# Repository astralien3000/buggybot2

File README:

This is the repository of buggybot 2, a four-legged robot which will take part to the robotic contest Eurobot.

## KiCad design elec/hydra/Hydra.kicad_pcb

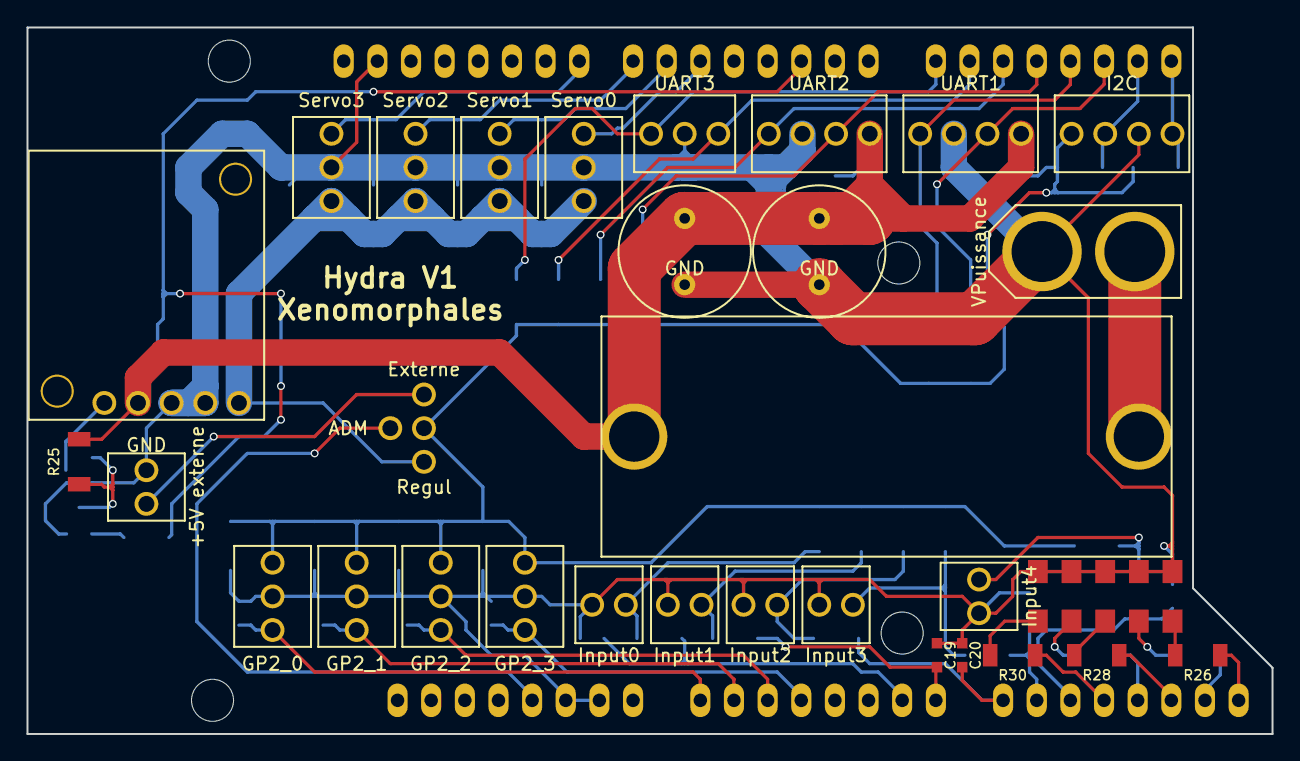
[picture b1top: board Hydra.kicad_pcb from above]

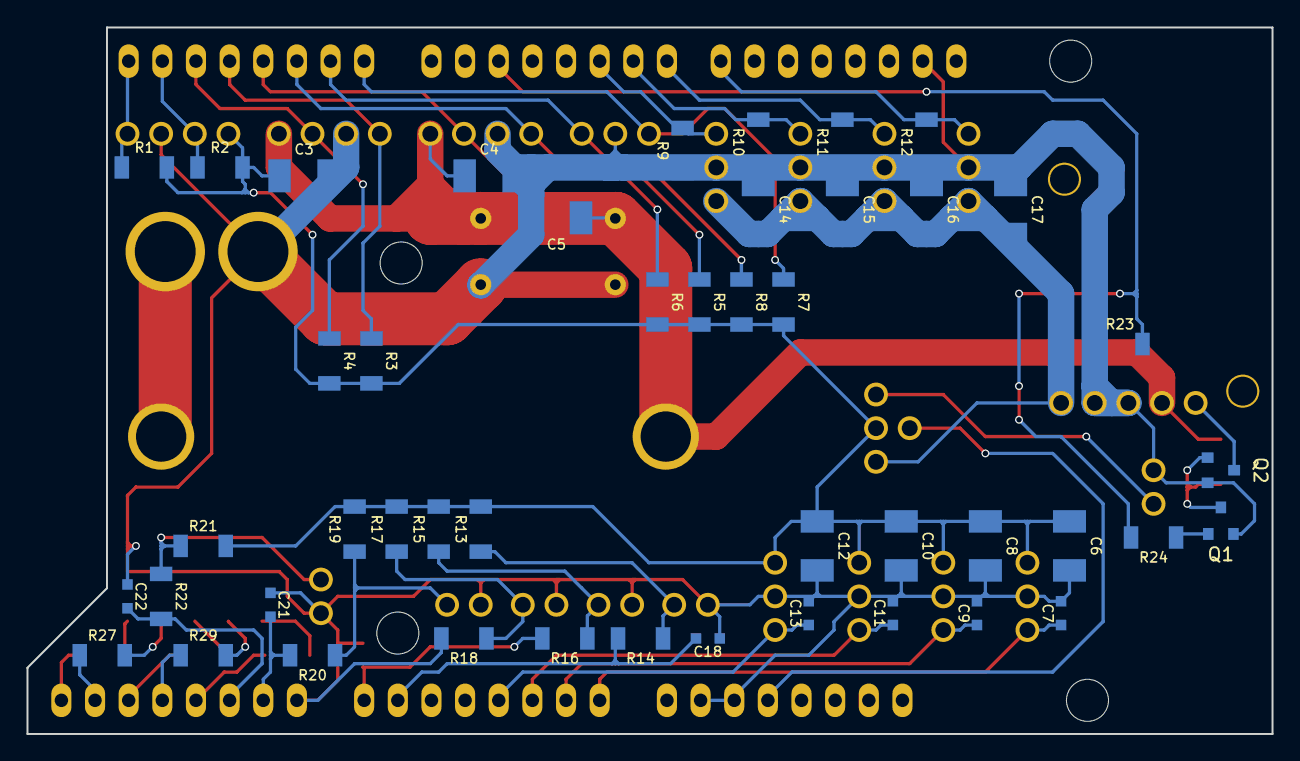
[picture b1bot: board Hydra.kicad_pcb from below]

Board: 2 copper layers, 94.0 x 53.3 mm, 82 parts (46 on the bottom side), 47 nets.

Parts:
+5V externe: Bat5V; Conn_01x02
C1, C2: 330µF; C_Radial
C3, C4, C5, C6, C8, C10, C12, C14, C15, C16, C17: 10µF; C_CMS1210
C7, C9, C11, C13: 100nF; C_CMS0603
C18, C19, C20, C21, C22: 1µF; C_CMS0603
D1, D2, D3, D4, D5: LED; LED_Green_CMS
F1: FUSE 20A; Fuse
GP2_0, GP2_1, GP2_2, GP2_3: GP2; Conn_01x03
I2C: I2C_1; Conn_01x04
Input0, Input1, Input2, Input3, Input4: Switch; Conn_01x02
P20: Jumper5V; 3-state_jumper
Q1, Q2: Q_NPN_BEC; SOT-23-3-bipolar-transistor
R1, R2, R3, R4, R5, R6, R7, R8, R9, R10, R11, R12, R23: 10kΩ; R_CMS1206
R13, R15, R17, R19, R21: 100kΩ; R_CMS1206
R14, R16, R18, R20, R22: 18kΩ; R_CMS1206
R24, R25: 1kΩ; R_CMS1206
R26, R27, R28, R29, R30: 200Ω; R_CMS1206
Regul1: Regul; Pololu_D24V50F5
SHIELD1: ARDUINO_MEGA_SHIELD
Servo0, Servo1, Servo2, Servo3: Servo; Conn_01x03
UART1: UART_1; Conn_01x04
UART2: UART_2; Conn_01x04
UART3: UART_3; Conn_01x03
VPuissance: Bat7.5V; Power_Conn_01x02

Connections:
/Arduino/+5VADM: P20.2, SHIELD1.5V
/Arduino/GND: +5V externe.1, C1.2, C2.2, C3.1, C4.1, C5.1, C6.1, C7.1, C8.1, C9.1, C10.1, C11.1, C12.1, C13.1, C14.2, C15.2, C16.2, C17.2, C18.2, C19.2, C20.2, C21.2, C22.2, D1.1, D2.1, D3.1, D4.1, D5.1, GP2_0.2, GP2_1.2, GP2_2.2, GP2_3.2, I2C.2, Input0.1, Input1.1, Input2.1, Input3.1, Input4.1, Q1.2, Q2.2, R9.2, R10.2, R11.2, R12.2, R23.2, Regul1.3, Regul1.4, SHIELD1.GND1, SHIELD1.GND2, SHIELD1.GND3, Servo0.2, Servo1.2, Servo2.2, Servo3.2, UART1.2, UART2.2, UART3.2, VPuissance.1
/Arduino/GP2_0: C7.2, GP2_0.1, SHIELD1.AD0
/Arduino/GP2_1: C9.2, GP2_1.1, SHIELD1.AD1
/Arduino/GP2_2: C11.2, GP2_2.1, SHIELD1.AD2
/Arduino/GP2_3: C13.2, GP2_3.1, SHIELD1.AD3
/Arduino/Input0: C18.1, R14.1, SHIELD1.AD6
/Arduino/Input1: C19.1, R16.1, SHIELD1.AD7
/Arduino/Input2: C20.1, R18.1, SHIELD1.AD8
/Arduino/Input3: C21.1, R20.1, SHIELD1.AD9
/Arduino/Input4: C22.1, R22.1, SHIELD1.AD10
/Arduino/RX1: R4.2, SHIELD1.19, UART1.3
/Arduino/RX2: R6.2, SHIELD1.17, UART2.3
/Arduino/RX3: R8.2, SHIELD1.15, UART3.3
/Arduino/RegulEnable: R23.1, R24.1, SHIELD1.2
/Arduino/SCL: I2C.1, R1.2, SHIELD1.21
/Arduino/SDA: I2C.3, R2.2, SHIELD1.20
/Arduino/TX1: R3.2, SHIELD1.18, UART1.1
/Arduino/TX2: R5.2, SHIELD1.16, UART2.1
/Arduino/TX3: R7.2, SHIELD1.14, UART3.1
/Com/+5V: C3.2, C6.2, C8.2, C10.2, C12.2, GP2_0.3, GP2_1.3, GP2_2.3, GP2_3.3, I2C.4, P20.4, R1.1, R2.1, R3.1, R4.1, R5.1, R6.1, R7.1, R8.1, R13.1, R15.1, R17.1, R19.1, R21.1
/Com/+7.5V: C1.1, C2.1, C4.2, C5.2, F1.1, R25.2, Regul1.2, UART1.4, UART2.4
/Servo1/+5V: C14.1, C15.1, C16.1, C17.1, P20.1, Regul1.5, Servo0.1, Servo1.1, Servo2.1, Servo3.1
/Servo1/PWM: R9.1, SHIELD1.5, Servo0.3
/Servo2/PWM: R10.1, SHIELD1.6, Servo1.3
/Servo3/PWM: R11.1, SHIELD1.7, Servo2.3
/Servo4/PWM: R12.1, SHIELD1.8, Servo3.3
unnamed: D1.2, R26.1
unnamed: D2.2, R27.1
unnamed: D3.2, R28.1
unnamed: D4.2, R29.1
unnamed: D5.2, R30.1
unnamed: F1.2, VPuissance.2
unnamed: Input0.2, R13.2, R14.2
unnamed: Input1.2, R15.2, R16.2
unnamed: Input2.2, R17.2, R18.2
unnamed: Input3.2, R19.2, R20.2
unnamed: Input4.2, R21.2, R22.2
unnamed: +5V externe.2, P20.3
unnamed: Q1.1, R24.2
unnamed: Q1.3, Q2.1, R25.1
unnamed: Q2.3, Regul1.1
unnamed: R26.2, SHIELD1.AD15
unnamed: R27.2, SHIELD1.AD14
unnamed: R28.2, SHIELD1.AD13
unnamed: R29.2, SHIELD1.AD12
unnamed: R30.2, SHIELD1.AD11

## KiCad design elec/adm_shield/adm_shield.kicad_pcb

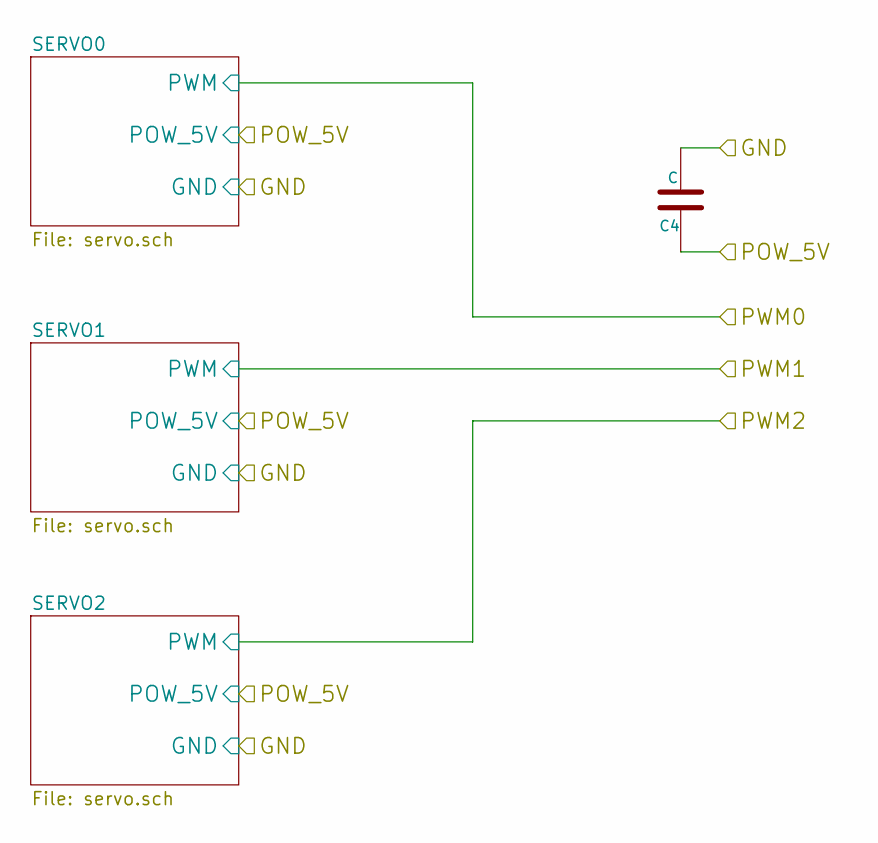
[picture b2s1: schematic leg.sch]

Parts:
C1: C

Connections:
/ALIM/GND: C1.2; also elsewhere on the board
/ALIM/POW_5V: C1.1; also elsewhere on the board

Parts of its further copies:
C2, C3, C4: C

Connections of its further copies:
/ALIM/GND: C2.2, C3.2, C4.2; also elsewhere on the board
/ALIM/POW_5V: C2.1, C3.1, C4.1; also elsewhere on the board

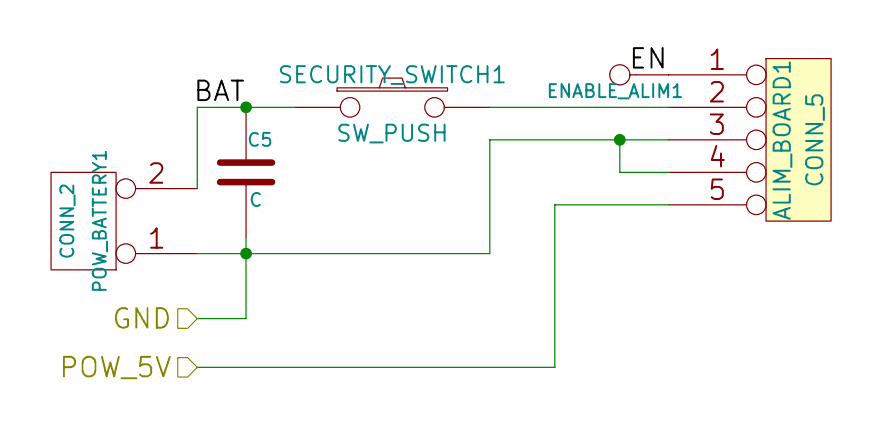
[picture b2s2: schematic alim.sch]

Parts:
ALIM_BOARD1: CONN_5
C5: C
ENABLE_ALIM1: CONN_1
POW_BATTERY1: CONN_2
SECURITY_SWITCH1: SW_PUSH

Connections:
/ALIM/BAT: C5.1, POW_BATTERY1.2 (PM), SECURITY_SWITCH1.1
/ALIM/EN: ALIM_BOARD1.1, ENABLE_ALIM1.1
/ALIM/GND: ALIM_BOARD1.3, ALIM_BOARD1.4, C5.2, POW_BATTERY1.1; also elsewhere on the board
/ALIM/POW_5V: ALIM_BOARD1.5; also elsewhere on the board
unnamed: ALIM_BOARD1.2, SECURITY_SWITCH1.2

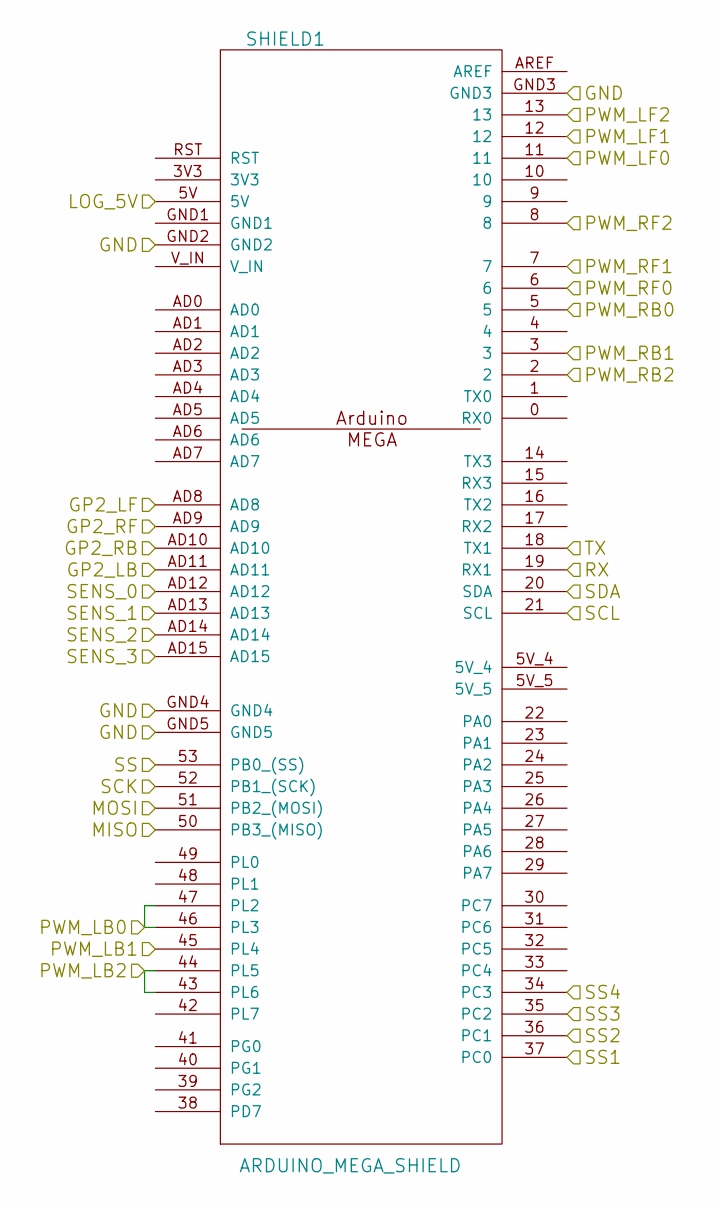
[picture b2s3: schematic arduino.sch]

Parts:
SHIELD1: ARDUINO_MEGA_SHIELD

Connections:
/ALIM/GND: SHIELD1.GND2, SHIELD1.GND3, SHIELD1.GND4, SHIELD1.GND5; also elsewhere on the board
/ARDUINO/GP2_LB: SHIELD1.AD11; also elsewhere on the board
/ARDUINO/GP2_LF: SHIELD1.AD8; also elsewhere on the board
/ARDUINO/GP2_RB: SHIELD1.AD10; also elsewhere on the board
/ARDUINO/GP2_RF: SHIELD1.AD9; also elsewhere on the board
/ARDUINO/LOG_5V: SHIELD1.5V; also elsewhere on the board
/ARDUINO/MISO: SHIELD1.50 (PB3_(MISO)); also elsewhere on the board
/ARDUINO/MOSI: SHIELD1.51 (PB2_(MOSI)); also elsewhere on the board
/ARDUINO/RX: SHIELD1.19 (RX1); also elsewhere on the board
/ARDUINO/SCK: SHIELD1.52 (PB1_(SCK)); also elsewhere on the board
/ARDUINO/SCL: SHIELD1.21 (SCL); also elsewhere on the board
/ARDUINO/SDA: SHIELD1.20 (SDA); also elsewhere on the board
/ARDUINO/SS: SHIELD1.53 (PB0_(SS)); also elsewhere on the board
/ARDUINO/SS1: SHIELD1.37 (PC0); also elsewhere on the board
/ARDUINO/SS2: SHIELD1.36 (PC1); also elsewhere on the board
/ARDUINO/SS3: SHIELD1.35 (PC2); also elsewhere on the board
/ARDUINO/SS4: SHIELD1.34 (PC3); also elsewhere on the board
/ARDUINO/TX: SHIELD1.18 (TX1); also elsewhere on the board
/GPIO/GPIO0: SHIELD1.AD12; also elsewhere on the board
/GPIO/GPIO1: SHIELD1.AD13; also elsewhere on the board
/GPIO/GPIO2: SHIELD1.AD14; also elsewhere on the board
/GPIO/GPIO3: SHIELD1.AD15; also elsewhere on the board
/LEG_LB/PWM0: SHIELD1.46 (PL3), SHIELD1.47 (PL2); also elsewhere on the board
/LEG_LB/PWM1: SHIELD1.45 (PL4); also elsewhere on the board
/LEG_LB/PWM2: SHIELD1.43 (PL6), SHIELD1.44 (PL5); also elsewhere on the board
/LEG_LF/PWM0: SHIELD1.11; also elsewhere on the board
/LEG_LF/PWM1: SHIELD1.12; also elsewhere on the board
/LEG_LF/PWM2: SHIELD1.13; also elsewhere on the board
/LEG_RB/PWM0: SHIELD1.5; also elsewhere on the board
/LEG_RB/PWM1: SHIELD1.3; also elsewhere on the board
/LEG_RB/PWM2: SHIELD1.2; also elsewhere on the board
/LEG_RF/PWM0: SHIELD1.6; also elsewhere on the board
/LEG_RF/PWM1: SHIELD1.7; also elsewhere on the board
/LEG_RF/PWM2: SHIELD1.8; also elsewhere on the board

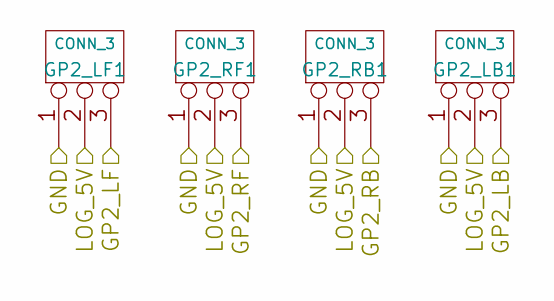
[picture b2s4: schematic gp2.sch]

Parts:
GP2_LB1, GP2_LF1, GP2_RB1, GP2_RF1: CONN_3

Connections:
/ALIM/GND: GP2_LB1.1, GP2_LF1.1, GP2_RB1.1, GP2_RF1.1; also elsewhere on the board
/ARDUINO/GP2_LB: GP2_LB1.3; also elsewhere on the board
/ARDUINO/GP2_LF: GP2_LF1.3; also elsewhere on the board
/ARDUINO/GP2_RB: GP2_RB1.3; also elsewhere on the board
/ARDUINO/GP2_RF: GP2_RF1.3; also elsewhere on the board
/ARDUINO/LOG_5V: GP2_LB1.2 (PM), GP2_LF1.2 (PM), GP2_RB1.2 (PM), GP2_RF1.2 (PM); also elsewhere on the board

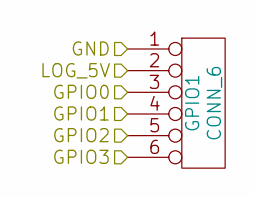
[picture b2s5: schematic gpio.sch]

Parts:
GPIO1: CONN_6

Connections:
/ALIM/GND: GPIO1.1; also elsewhere on the board
/ARDUINO/LOG_5V: GPIO1.2; also elsewhere on the board
/GPIO/GPIO0: GPIO1.3; also elsewhere on the board
/GPIO/GPIO1: GPIO1.4; also elsewhere on the board
/GPIO/GPIO2: GPIO1.5; also elsewhere on the board
/GPIO/GPIO3: GPIO1.6; also elsewhere on the board

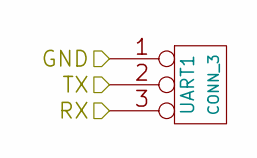
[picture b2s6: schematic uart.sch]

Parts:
UART1: CONN_3

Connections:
/ALIM/GND: UART1.1; also elsewhere on the board
/ARDUINO/RX: UART1.3; also elsewhere on the board
/ARDUINO/TX: UART1.2 (PM); also elsewhere on the board

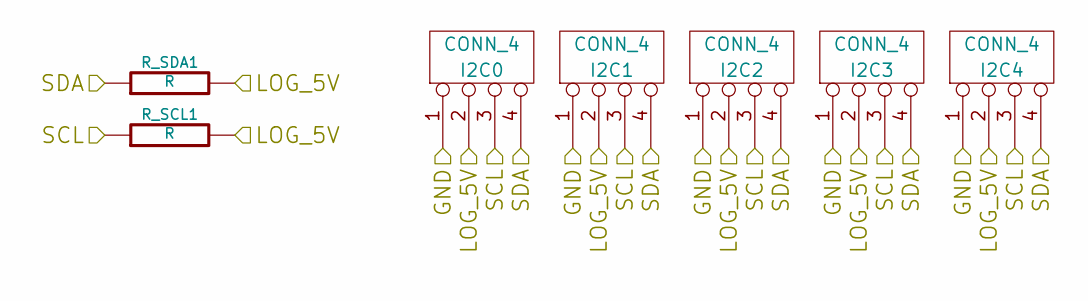
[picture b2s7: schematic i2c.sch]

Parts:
I2C0, I2C1, I2C2, I2C3, I2C4: CONN_4
R_SCL1: R
R_SDA1: R

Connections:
/ALIM/GND: I2C0.1, I2C1.1, I2C2.1, I2C3.1, I2C4.1; also elsewhere on the board
/ARDUINO/LOG_5V: I2C0.2, I2C1.2, I2C2.2, I2C3.2, I2C4.2, R_SCL1.2, R_SDA1.2; also elsewhere on the board
/ARDUINO/SCL: I2C0.3, I2C1.3, I2C2.3, I2C3.3, I2C4.3, R_SCL1.1; also elsewhere on the board
/ARDUINO/SDA: I2C0.4, I2C1.4, I2C2.4, I2C3.4, I2C4.4, R_SDA1.1; also elsewhere on the board

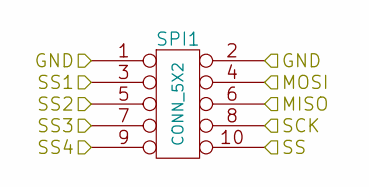
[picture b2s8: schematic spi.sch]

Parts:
SPI1: CONN_5X2

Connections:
/ALIM/GND: SPI1.1, SPI1.2; also elsewhere on the board
/ARDUINO/MISO: SPI1.6; also elsewhere on the board
/ARDUINO/MOSI: SPI1.4; also elsewhere on the board
/ARDUINO/SCK: SPI1.8; also elsewhere on the board
/ARDUINO/SS: SPI1.10; also elsewhere on the board
/ARDUINO/SS1: SPI1.3; also elsewhere on the board
/ARDUINO/SS2: SPI1.5; also elsewhere on the board
/ARDUINO/SS3: SPI1.7; also elsewhere on the board
/ARDUINO/SS4: SPI1.9; also elsewhere on the board

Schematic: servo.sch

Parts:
SERVO_LF1: CONN_3

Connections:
/ALIM/GND: SERVO_LF1.1; also elsewhere on the board
/ALIM/POW_5V: SERVO_LF1.2 (PM); also elsewhere on the board
/LEG_LF/PWM1: SERVO_LF1.3; also elsewhere on the board

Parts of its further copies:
SERVO_LB0, SERVO_LB1, SERVO_LB2: CONN_3
SERVO_LF0, SERVO_LF2: CONN_3
SERVO_RB0, SERVO_RB1, SERVO_RB2: CONN_3
SERVO_RF0, SERVO_RF1, SERVO_RF2: CONN_3

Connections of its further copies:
/ALIM/GND: SERVO_LB0.1, SERVO_LB1.1, SERVO_LB2.1, SERVO_LF0.1, SERVO_LF2.1, SERVO_RB0.1, SERVO_RB1.1, SERVO_RB2.1, SERVO_RF0.1, SERVO_RF1.1, SERVO_RF2.1; also elsewhere on the board
/ALIM/POW_5V: SERVO_LB0.2 (PM), SERVO_LB1.2 (PM), SERVO_LB2.2 (PM), SERVO_LF0.2 (PM), SERVO_LF2.2 (PM), SERVO_RB0.2 (PM), SERVO_RB1.2 (PM), SERVO_RB2.2 (PM), SERVO_RF0.2 (PM), SERVO_RF1.2 (PM), SERVO_RF2.2 (PM); also elsewhere on the board
/LEG_LB/PWM0: SERVO_LB0.3; also elsewhere on the board
/LEG_LB/PWM1: SERVO_LB1.3; also elsewhere on the board
/LEG_LB/PWM2: SERVO_LB2.3; also elsewhere on the board
/LEG_LF/PWM0: SERVO_LF0.3; also elsewhere on the board
/LEG_LF/PWM2: SERVO_LF2.3; also elsewhere on the board
/LEG_RB/PWM0: SERVO_RB0.3; also elsewhere on the board
/LEG_RB/PWM1: SERVO_RB1.3; also elsewhere on the board
/LEG_RB/PWM2: SERVO_RB2.3; also elsewhere on the board
/LEG_RF/PWM0: SERVO_RF0.3; also elsewhere on the board
/LEG_RF/PWM1: SERVO_RF1.3; also elsewhere on the board
/LEG_RF/PWM2: SERVO_RF2.3; also elsewhere on the board

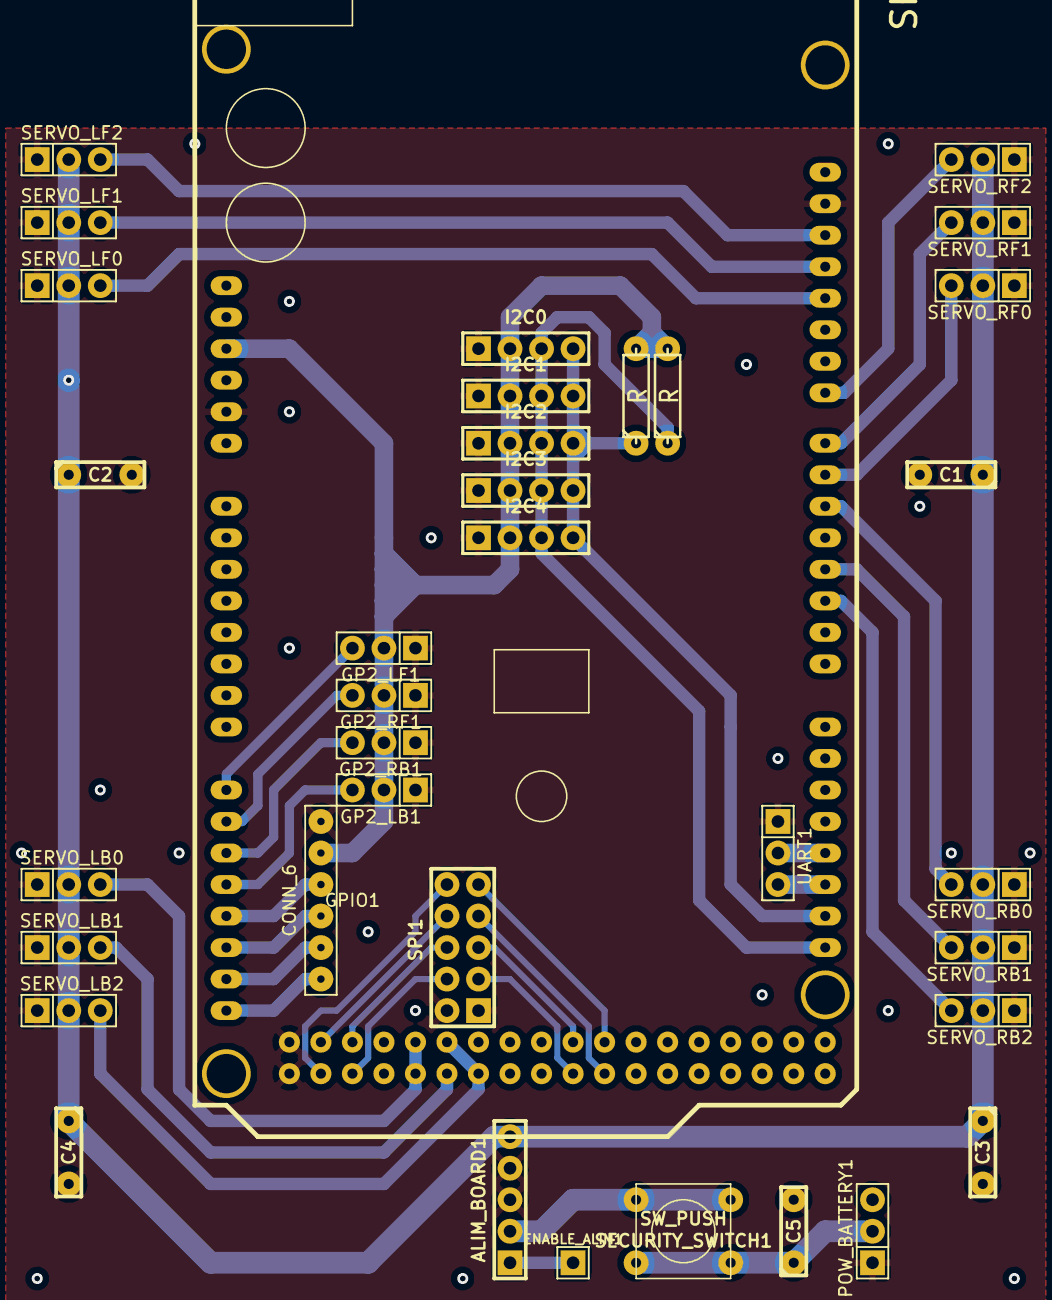
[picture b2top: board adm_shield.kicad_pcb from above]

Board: 2 copper layers, 36 parts (0 on the bottom side), 38 nets.

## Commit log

2014-10-30 Begining
2014-10-30 Added tr_homogene.mac
2014-10-30 MGD, begining
2014-11-01 Added gitignore
2014-11-01 Added old test of multipwm
2014-11-01 Added .hex files to gitignore
2014-11-01 Multipwm example now compiles
2014-11-01 Added servo_config
2014-11-01 Separation of servo_tester
2014-11-02 Created a shell for calibration
2014-11-02 Added QtCreator files
2014-11-02 Added .gitignore to qtcreator dir
2014-11-12 Added MGI
2014-11-12 Renamed some files
2014-11-12 Moved some utils function in a separate file
2014-11-12 added some fake measures
2014-11-12 added cinematic model
2014-11-14 Modified a little MGI and MGD
2014-11-16 Changed compile chain to cmake
2014-11-18 Added .gitignore to build dir in calib
2014-11-18 Added coeff eq paul
2014-11-19 Added paul8 function
2014-11-19 Added .gitignore to meca/solve
2014-11-24 Mesh generation script.
2014-11-25 Added MGI and MGD to blender simulation
2014-11-28 simu MGD and MGI
2014-11-28 Communicaton between robot and computer works ! The robot can "walk". Servo are calibrated
2015-02-27 Begin to designe arduino shield.
2015-02-27 Modified servos (120Hz -> 60Hz)
2015-02-27 Continuation of Kicad schematics.
2015-02-28 Schematics finished ?
2015-02-28 Begining of the PCB.
2015-02-28 PCB almost finished ?
2015-02-28 First version PCB.
2015-03-01 Shield V2 (PCB begining)
2015-03-01 Before routing.
2015-03-01 PCB almost finished !
2015-03-01 PCB FINISHED ! + Correction of schematics.
2015-03-01 Modified ServoTester init. Modified Servos pin mapping. Added a security to SetAngle (0 div).
2015-03-02 PCB v3 !
2015-03-02 V3.1 ?
2015-03-06 New wlaking algo. PCB v4
2015-03-06 PCB v4.1
2015-03-14 Awesome new control program is working !!!
2015-03-15 Better connection management
2015-03-18 Turn and climb animations
2015-04-06 Added accelero test.
2015-04-11 Added astrabot protocol.
2015-04-11 Separated ap parser
2015-04-12 Test comm with arduino
2015-04-22 Added forgotten files. Added bumper management.
2015-04-26 GP2 managed. Added python AP parser.
2015-04-27 Added adc module.
2015-04-27 Added files to .gitignore
2015-04-27 Moved soft directories
2015-04-27 Moved files in soft/embed (WARNING -> doesn't compile)
2015-04-27 Protocol test now compiles !
2015-04-27 ADC test compiles !
2015-04-27 Added cleaning script to embed
2015-04-27 ap_server now compiles !
2015-04-29 Updated MGD model. MGI have to be changed, but gives values near from Blender's ones.
2015-04-29 Updated MGI to new meca
2015-04-29 New MGI implemented in python !!!
2015-05-01 NEW CALIB (WEB) APPLICATION
2015-05-01 Added run.sh script
2015-05-01 Debug MGI !
2015-05-02 Cleaned MGD code
2015-05-02 Cleaned blend file
2015-05-02 Improved animation
2015-05-02 Comm blender - robot works !
2015-05-03 Animation PASSMURAILLE
2015-05-03 Blender-independent code
2015-05-03 Exported crawl anim
2015-05-03 Debug save.py
2015-05-03 debug anim length dependency
2015-05-03 Added old walk anim improved
2015-05-03 Walk anim
2015-05-03 Added turn anim
2015-05-14 Homologation
2015-05-14 Updated gitignore
2015-05-14 NEW CRAWL ANIM !!!
2015-05-15 Begin Match
2015-05-15 Improved turn anim
2015-05-15 New walk anim
2015-05-15 Match improvement
2015-05-15 Match almost done ?
2015-05-15 Final Match ?
2015-05-15 Some debug
2015-05-16 Dance
2015-05-16 teleoperation code
2015-05-23 Last match modified.
2015-09-01 Calib with 31kg servo
2015-09-01 Begining of new elec board
2015-09-02 Completed new board schematics.
2015-09-17 Added autodesk meca
2015-11-07 Elec ?
2015-11-07 Big dirty commit
2015-11-07 Meca
2015-11-08 Moved old strategy code to test dir
2015-11-08 First DDS Node
2015-11-08 Moved old files in test dir
2015-11-08 Implementation of MGD in c++
2015-11-08 Finished BodyPoseNode
2015-11-12 Begining of blender node
2015-11-26 BlenderViz implementation (not finished)
2016-01-09 Slowed down test node.
2016-01-10 Moved DDS node initialization to a lib
2016-03-26 Reorganized soft directory
2016-03-28 rm all
2016-03-29 Added embed app
2016-03-29 Added .gitignore
2016-03-29 Added embed-controller app
2016-03-29 Added protocol lib
2016-03-29 Added some payloads for later
2016-03-31 Added servo communication
2016-04-02 Begining of ZMQ network
2016-04-02 First communication through ZMQ network
2016-04-04 Merged zmq embed sockets
2016-04-04 Lowered cmake version required
2016-04-04 Begining of web-ui
2016-04-04 First test of ZMQ with node.js
2016-04-04 Debug config serialization (cereal doesn't handle JSON "inf" value)
2016-04-05 Debug servo-mapper
2016-04-05 servo-mapper fully configurable
2016-04-05 Begining of web interface
2016-04-06 Web ui can get and set config
2016-04-06 Web ui can display current angle and position. Added 'enabled' attributes to servo messages
2016-04-06 [servo-mapper] Add default id to new servo.
2016-04-06 [web-ui] Disconnect zmq when client disconnect
2016-04-09 Added buggybot blender mode with armature
2016-04-09 Added first draft for ik export
2016-04-09 Removed old meca
2016-04-09 improved ik exporter
2016-04-09 Added *.blend1 rule to .gitignore
2016-04-09 ik_export script completed
2016-04-09 Added ik application. Test ik ik_export compiles
2016-04-09 ik_export debug
2016-04-09 Full IK compiled
2016-04-09 Refactored ik app
2016-04-10 Implementation of RobotModel in ik app
2016-04-10 Rotation of the model to make the left front leg into positive x and y coordinates.
2016-04-11 Added messages lib
2016-04-11 Config ik angles convertion
2016-04-11 Implemented ik zmq io (not tested)
2016-04-11 Added "NONE" leg
2016-04-11 First integration (~working)
2016-04-11 Debug of arduino random reset
2016-04-11 All servos connected !
2016-04-13 Test with 4 legs
2016-04-13 Complete walk animation
2016-04-15 Add embed-test. Improve communication system.
2016-04-18 embed-controller error handle improved
2016-04-18 Improved messaging systems
2016-04-18 Reenabled web-ui
2016-04-18 Improved communication config + added -O3 to ik app
2016-04-19 Removed embed-controller dependency on QtWidget (QApplication -> QCoreApplication)
2016-04-19 Removed debug display in ik app
2016-04-19 Added optoforce node
2016-04-19 Renamed optoforce sensors
2016-04-20 Calibration of optoforce ik !
2016-04-29 Reset default servo values
2016-05-01 Added ADC and PWM drivers
2016-05-01 Servo OK
2016-05-02 Debug GPIO input
2016-05-02 Test Regulator Enable (not working because of electronics)
2016-05-03 gp2.in and bumper.in sockets created
2016-05-04 Begining coupe
2016-05-05 Homologation 2
2016-05-05 Debug communication
2016-05-06 Match2
2016-05-10 Dirty teleoperation client/server
2016-05-12 Debug servo-mapper config messages when no config available
2016-08-28 Various debugs + error messages.
2016-08-30 Adding Hydra board files
2016-08-31 Clean elec directory
2016-09-09 Removed old arduino shield
2016-09-10 Clean ros test
2016-09-10 fakeros begining
2016-09-10 Improved servo-mapper config management
2016-09-10 Modified ServoConfig (not using exception anymore)
2016-09-10 Dirty coap server in fakeros impl
2016-09-10 Dirty implementation test
2016-09-10 Dirty test
2016-09-18 Replaced buggybot3's meca by buggybot4's meca
2016-09-22 Update soft to buggybot4 mega
2016-10-02 Better animations (teleopt) !
2016-10-26 Added ik-test
2016-10-27 Big debug
2016-10-27 Better perfs
2016-10-28 embed-test-ik
2016-10-30 apps reorganisation
2016-10-30 Clean teleopt-client
2016-11-09 removed dependencies on Qt and Aversive++ for ik
2016-11-09 Removed dependency on Qt and Aversive++ for teleopt-server
2016-11-09 Removed dependency on Aversive++ for serial-controller
2016-11-10 Update to newer Aversive++
2016-11-14 serial-controller using conan
2016-11-15 target.mcu => target
2016-11-15 Added Makefiles
2016-11-15 Added 2 run modes in Makefile
2016-11-18 Update CMakeLists + Update teleopt-server and ik nodes to new Aversive++
2016-11-25 Begining IoTLab demo
2016-11-25 Debug
2016-11-28 Improved .gitignore
2016-11-29 Moved teleopt-iotlab in iotlab/teleopt-client
2016-11-30 Begin embed-io
2016-12-02 Working embed-io
2016-12-02 embed-io with AnimHandler
2016-12-05 Improved embed-io build system
2016-12-05 iotlab/fwd test node
2016-12-07 embed-ik working on SAMR21
2016-12-13 New fwd
2016-12-14 Improved coap--
2016-12-15 Begin dirty embed-full implementation
2016-12-16 embed-full working !
2016-12-17 Added turn animation to embed-full
2017-01-20 Added command_handler
2017-01-23 Added Stand animation.
2017-01-23 Added alive thread
2017-01-23 Working iot-lab demo
2017-02-09 toolchain-switch -> cmake-toolchain
2017-02-09 Modify to fit new API
